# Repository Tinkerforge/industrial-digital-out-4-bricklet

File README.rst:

Industrial Digital Out 4 Bricklet
=================================

This repository contains the firmware source code and the hardware design
files. The documentation generator configs can be found at
https://github.com/Tinkerforge/generators

Repository Content
------------------

software/:
 * examples/: Examples for all supported languages
 * build/: Compiled files
 * src/: Source code of firmware
 * Makefile: Makefile to build project

hardware/:
 * Contains KiCad project files and additionally schematics as PDF

datasheets/:
 * Contains datasheets for sensors and complex ICs that are used

Hardware
--------

The hardware is designed with the open source EDA Suite KiCad
(http://www.kicad.org). Before you are able to open the files,
you have to install the Tinkerforge kicad-libraries
(https://github.com/Tinkerforge/kicad-libraries). You can either clone
them directly in hardware/ or clone them in a separate folder and
symlink them into hardware/
(ln -s kicad_path/kicad-libraries project_path/hardware). After that you
can open the .pro file in hardware/ with KiCad and from there view and
modify the schematics and the PCB layout.

Software
--------

If you want to do your own Brick/Bricklet firmware development we highly
recommend that you use our build environment setup script and read the
tutorial (https://www.tinkerforge.com/en/doc/Tutorials/Tutorial_Build_Environment/Tutorial.html).

To compile the C code we recommend you to install the newest GNU Arm Embedded
Toolchain (https://launchpad.net/gcc-arm-embedded/+download).
You also need to install bricklib (https://github.com/Tinkerforge/bricklib)
and brickletlib (https://github.com/Tinkerforge/brickletlib).

You can either clone it directly in software/src/ or clone it in a
separate folder and symlink it into software/src/
(ln -s bricklib_path/bricklib project_path/software/src/ and
ln -s brickletlib_path/brickletlib project_path/software/src/).
Finally make sure to have CMake installed
(http://www.cmake.org/cmake/resources/software.html).

After that you can build the firmware by invoking make in software/.
The firmware (.bin) can then be found in software/build/ and uploaded
with brickv (click button "Flashing" on start screen).

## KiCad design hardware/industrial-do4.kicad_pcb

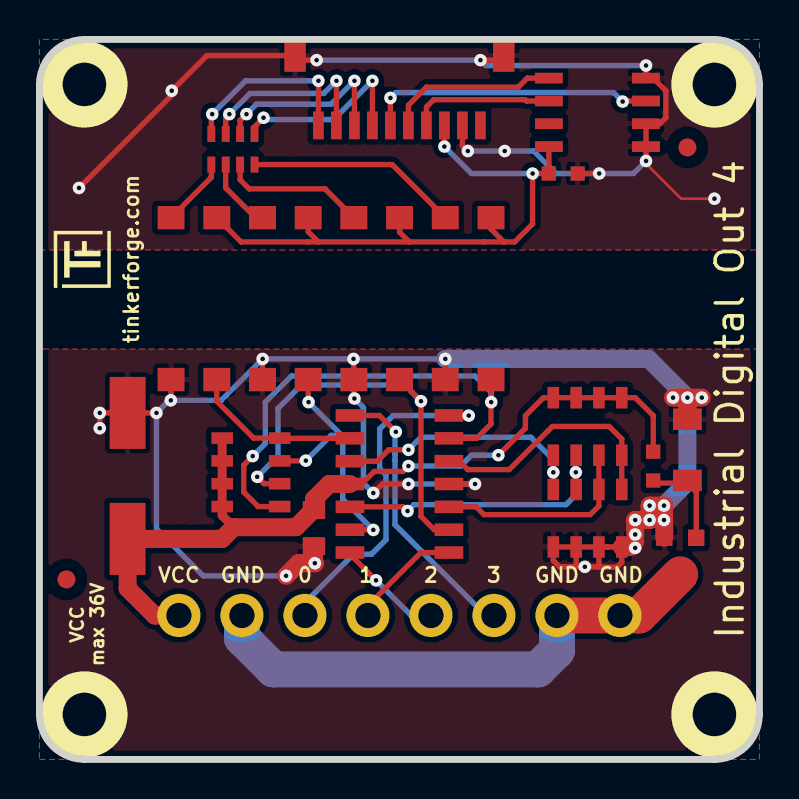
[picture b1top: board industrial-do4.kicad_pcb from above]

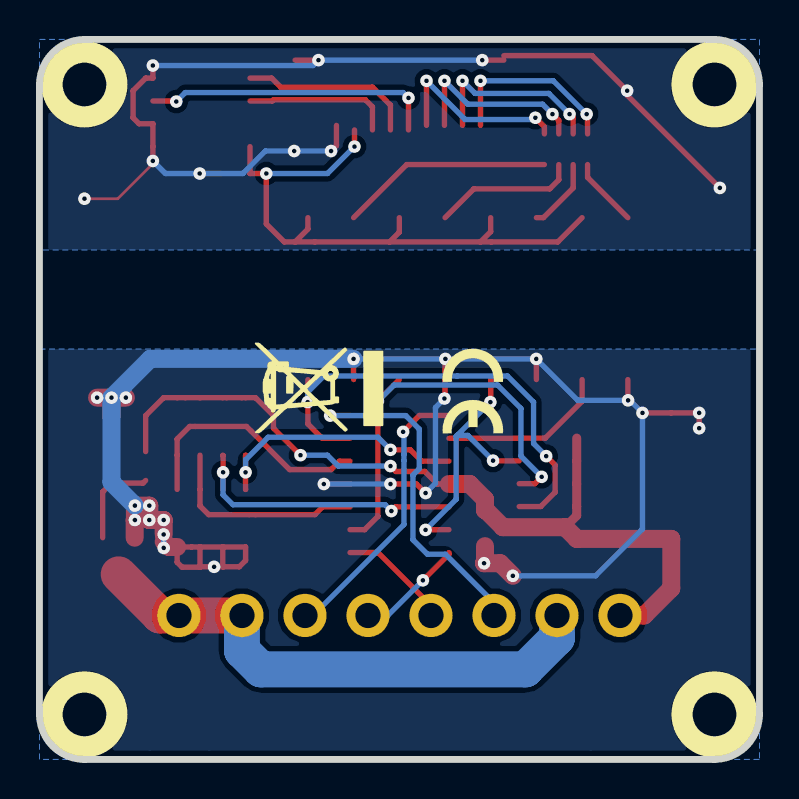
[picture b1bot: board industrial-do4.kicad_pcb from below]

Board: 2 copper layers, 40.0 x 40.0 mm, 23 parts (2 on the bottom side), 29 nets.

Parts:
C1: 100nF; C0603
C2: 100nF; C0805
C3: 68µF/50V; ELKO_83
D1: Z12V; MiniMelf
Fiducial_Mark: VAL**; Fiducial_Mark
Fiducial_Mark#2: VAL**; Fiducial_Mark
P1: CON-SENSOR
P2: Digital Output; OQ_8P
Q1: FDN5630; SOT23GDS
R1: 100k; R0603
RP1: 1k; 0603X4
RP2: 12k; 1206X4
RP3, RP4: 10k; 1206X4
U1: M24C64; SOIC8
U2: LTV846S; OPTO-SMD16
U3: OPA4171AIDR; SOP14
U4, U5, U6, U7: DRILL; DRILL_NP
VAL: WEEE_7mm
VAL#2: CE_5mm

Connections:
3V3: C1.1, P1.3, U1.8, U2.1, U2.3, U2.5, U2.7
AGND: C2.2, C3.2, D1.1, Q1.S, RP4.1, RP4.2, RP4.3, RP4.4, U2.9, U2.11, U2.13, U2.15, U3.11
GND: C1.2, P1.2, P1.EP, U1.1, U1.2, U1.4
unnamed: D1.2, Q1.G, R1.2
unnamed: P1.4, U1.6
unnamed: P1.5, U1.5
unnamed: P1.6, U1.3
unnamed: P2.2, P2.7, P2.8, Q1.D
unnamed: P2.3, U3.14
unnamed: P2.4, U3.8
unnamed: P2.5, U3.7
unnamed: P2.6, U3.1
unnamed: RP1.5, U2.8
unnamed: RP1.6, U2.6
unnamed: RP1.7, U2.4
unnamed: RP1.8, U2.2
unnamed: RP2.1, U2.16, U3.13
unnamed: RP2.2, U2.14, U3.9
unnamed: RP2.3, U2.12, U3.6
unnamed: RP2.4, U2.10, U3.2
unnamed: RP3.1, RP4.8, U3.3
unnamed: RP3.2, RP4.7, U3.5
unnamed: RP3.3, RP4.6, U3.10
unnamed: RP3.4, RP4.5, U3.12
OUTPUT1: P1.7, RP1.1
OUTPUT2: P1.8, RP1.2
OUTPUT3: P1.9, RP1.3
OUTPUT4: P1.10, RP1.4
VPP: C2.1, C3.1, P2.1, R1.1, RP2.5, RP2.6, RP2.7, RP2.8, RP3.5, RP3.6, RP3.7, RP3.8, U3.4

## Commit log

2012-09-24 Test for NULL and use uint16 for value instead of uint8
2012-10-24 Make cmake find the correct objcopy binary
    On some systems cmake uses the wrong objcopy binary, tell it to use
    the correct one.
2012-11-13 Support for protocol 2.0
2012-11-23 Add examples for c, csharp, delphi, java, php, python and ruby
2012-11-23 Fix typo
2012-11-23 php: Fix indenation
2012-11-28 Add Industrial Digital Out 4 hardware files
2012-11-28 Add checks for unused pins and fix inverted values
2012-11-28 Fix parameter order in com_return_error calls
    Fix error handling in set_group.
2012-11-29 Make examples compatible to Protocol V2.0
2012-11-29 Make Ruby examples Protocol 2.0 compatible
2012-11-29 Make C examples Protocol 2.0 compatible
2012-11-29 Make Java examples Protocol 2.0 compatible
2012-11-29 Make Delphi/Pascal examples Protocol 2.0 compatible
2012-11-30 delphi: Remove unnecessary parentheses and call destructor again
2012-12-05 Add protocol 2.0 compatability to C# bindings
2013-01-14 Add possibility to set selected values to API
2013-02-07 Use IPconnection disconnect explicitly in examples
2013-02-18 Add Visual Basic .NET examples
2013-07-17 Break long lines
2013-08-12 Add shell example
2013-08-12 shell: Explain magic value
2013-08-21 windows: Don't trigger a build in generate_makefile.bat
    Also use normal make instead of a special named one.
2014-01-10 Add Perl examples
2014-01-15 php: Use const for constant values
2014-02-07 Add Mathematica examples
2014-02-10 perl: fixed namespace
2014-02-11 javascript: adding examples
2014-02-11 javascript: short examples
2014-02-18 javascript: examples fixed
2014-02-20 javascript: adding html examples
2014-02-24 javascript: port 4280, startExample()
2014-02-28 javascript: Break long lines and cleanup whitespace
2014-03-05 Add LabVIEW example
2014-03-06 labview: Add example in LV2010 format
2014-03-27 matlab: add examples
2014-04-02 java: Unify constants style
2014-04-02 perl: Unify print style
2014-04-17 matlab: Adapt examples to new callback style
2014-04-17 matlab: Add parentheses to make pygments happy
2014-07-15 java: Replace System.console() usage with an Eclipse compatible pattern
2014-09-18 Add op-amp datasheet
2014-12-02 Use ReadLine instead of ReadKey for C# example
2015-02-13 vbnet: Use ReadLine instead of ReadKey
    Because ReadKey doesn't work with a pipe as stdin on the RED Brick.
2015-03-02 windows: Stop cmake from searching for mingw32-make.exe
    Using MinGW Makefiles as generator makes cmake search for mingw32-make.exe
    which might not be installed because GnuWin32's make.exe is used instead.
2015-03-26 update to latest hardware files
2015-04-09 c: Whitespace
2015-06-23 perl: Fix typo
2015-07-23 Make JavaScript browser example textarea readonly
2015-07-27 Cleanup C/C++, C#, Java, Python and Ruby examples
2015-07-29 Reformat changelog
2015-08-07 Use full device class name in Python example
2015-08-12 Fix minor warnings in C/C++ example
2015-08-14 Cleanup Delphi example
2015-08-18 Unify example loop logic
2015-08-18 Cleanup VB.NET examples
2015-09-09 Remove possible compile warning from example
2015-09-09 Duplicate cmake call to fix bug during cmake creation
2015-10-08 Generator based example cleanup
2015-11-12 matlab: Fix callback handling for R2014a
    http://undocumentedmatlab.com/blog/matlab-callbacks-for-java-events-in-r2014a
2015-11-25 Include date and commit into changelog
2016-05-18 c: Add missing device destroy call
2016-06-29 Whitespace
2016-07-01 Make the change UID comment more explicit
2016-09-02 adapt capacitor value to 68µF
2017-06-02 octave: Use javaObject instead of deprecated java_new
2017-07-28 Fix broken symbols and broken orientation
2017-07-28 Add 3d information (final)
2017-07-28 add missing pcb file
2017-07-28 Add 3d information (tbc)
2017-07-31 Add 3d model (*.step & *.FCStd)
2017-07-31 Rename *.FCStd file
2017-12-07 mathematica: Also generate .nb files
2018-01-26 c: Fine-tune define placement
2018-02-19 javascript: Close div tag correctly
2018-02-20 Cleanup KiCad libraries config
    Ensure LibDir=kicad-libraries and LibName1=tinkerforge.
    Remove special library.
2018-05-11 Rename files
2018-05-11 Rename files correctly
2018-05-24 perl: Use strict in examples
2018-07-11 Add Makefile with docker support
2018-07-11 Update directory structure and build instructions
2018-07-11 Remove obsolete generate_makefile scripts
2018-09-10 Better wording in examples
2018-11-06 Add rust examples
2018-11-07 rust: Accept host names for ip connection, fix naming inconsistencies
2018-12-14 Add go examples.
2018-12-18 go: Change import path.
2018-12-18 go: Change import path again.
2018-12-20 rust: Reformat examples.
2019-01-24 mqtt: Add examples.
2019-01-24 mqtt: Fix example header.
2019-01-24 mqtt: Remove executable bit in example permissions.
2019-01-24 go: Minor example fixes.
2019-01-24 mqtt: Minor example fixes.
2019-01-29 rust: Fix unused loop index.
2020-01-13 examples: Use python3 input instead of python2 raw_input.
2020-01-13 examples: mqtt: Remove trailing whitespace.
2020-03-23 mqtt: Update for loop style
2020-04-07 examples: rust: Always block when calling bindings functions.
2021-10-25 Update KiCad link
    https://www.kicad.org/blog/2021/10/Avoid-links-to-former-kicad-domain/
2022-07-06 Add license files.

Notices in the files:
hardware/industrial-do4.kicad_pcb:
Copyright Tinkerforge GmbH 2012.
This documentation describes Open Hardware and is licensed under the
CERN OHL v. 1.1.
